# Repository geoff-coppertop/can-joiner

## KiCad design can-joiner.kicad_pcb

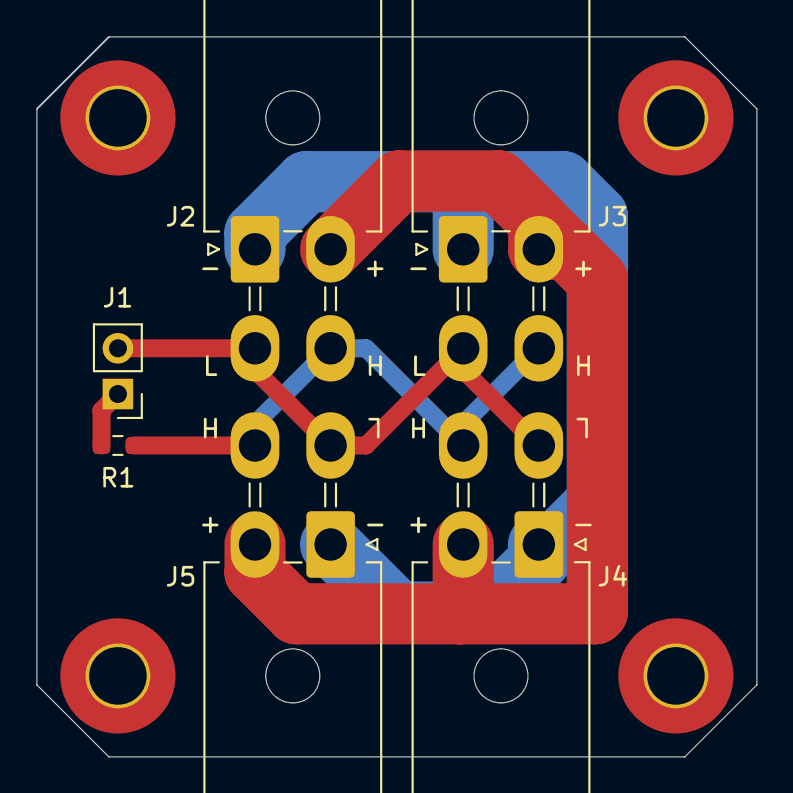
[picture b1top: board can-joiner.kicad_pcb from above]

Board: 2 copper layers, 40.0 x 40.0 mm, 10 parts (0 on the bottom side), 5 nets.

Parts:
H1, H2, H3, H4: MountingHole; MountingHole_3.2mm_M3_Pad_TopBottom
J1: Conn_01x02; PinHeader_1x02_P2.54mm_Vertical
J2, J3, J4, J5: Conn_02x02_Odd_Even; Molex_Mini-Fit_Jr_5569-04A2_2x02_P4.20mm_Horizontal
R1: 120R; R_0603_1608Metric_Pad0.98x0.95mm_HandSolder

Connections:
/CAN_DATA_SHUNT: J1.1, R1.2
/CAN_H: J2.4, J3.4, J4.4, J5.4, R1.1
/CAN_L: J1.2, J2.3, J3.3, J4.3, J5.3
GND: J2.1, J3.1, J4.1, J5.1
VCC: J2.2, J3.2, J4.2, J5.2
